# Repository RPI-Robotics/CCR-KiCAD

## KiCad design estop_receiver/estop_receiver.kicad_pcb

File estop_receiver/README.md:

# Emergency Stop Receiver

---

A custom board to wirelessly and securely interface with the Emergency Stop remote. Upon interfacing with the remote and confirming connection, the receiver will continuously scan for a heartbeat packet from the remote. If no heartbeat packet is received within 2 seconds, the receiver will trigger the failsafe to trigger the emergency stop. Upon receiving a STOP packet, the same emergency stop will trigger, pulling a high signal down to low within X ms.

This board is split into two different boards made to fabricate together and easily break apart from each other. One board is for LED indicators and the other is the board used to receive and interpret signals. Both are powered by 5V from the central power system.

**Status:** Version 1 Gerber and Drill files created. Ordering very soon (I hope).

## Schematic

---

**Rough breakdown:**

- Circuit takes two active low signals as input which are fed into an AND logic gate.

- AND gate controls an nMOS MOSFET which powers two Normally Open solid state relays.

- Upon the loss of one emergency stop signal, solid state relays shut off and indicator LED's switch.

## PCB Layout

---

PCB dimensions are 31mm x 56.5mm.

## ToDo List

---

- [x] Design PCB layout.

- [ ] Order board and parts.

- [ ] Assemble and test.

## Credits

---

Original design by James Qiu for RPI Robotics Club, 2026.

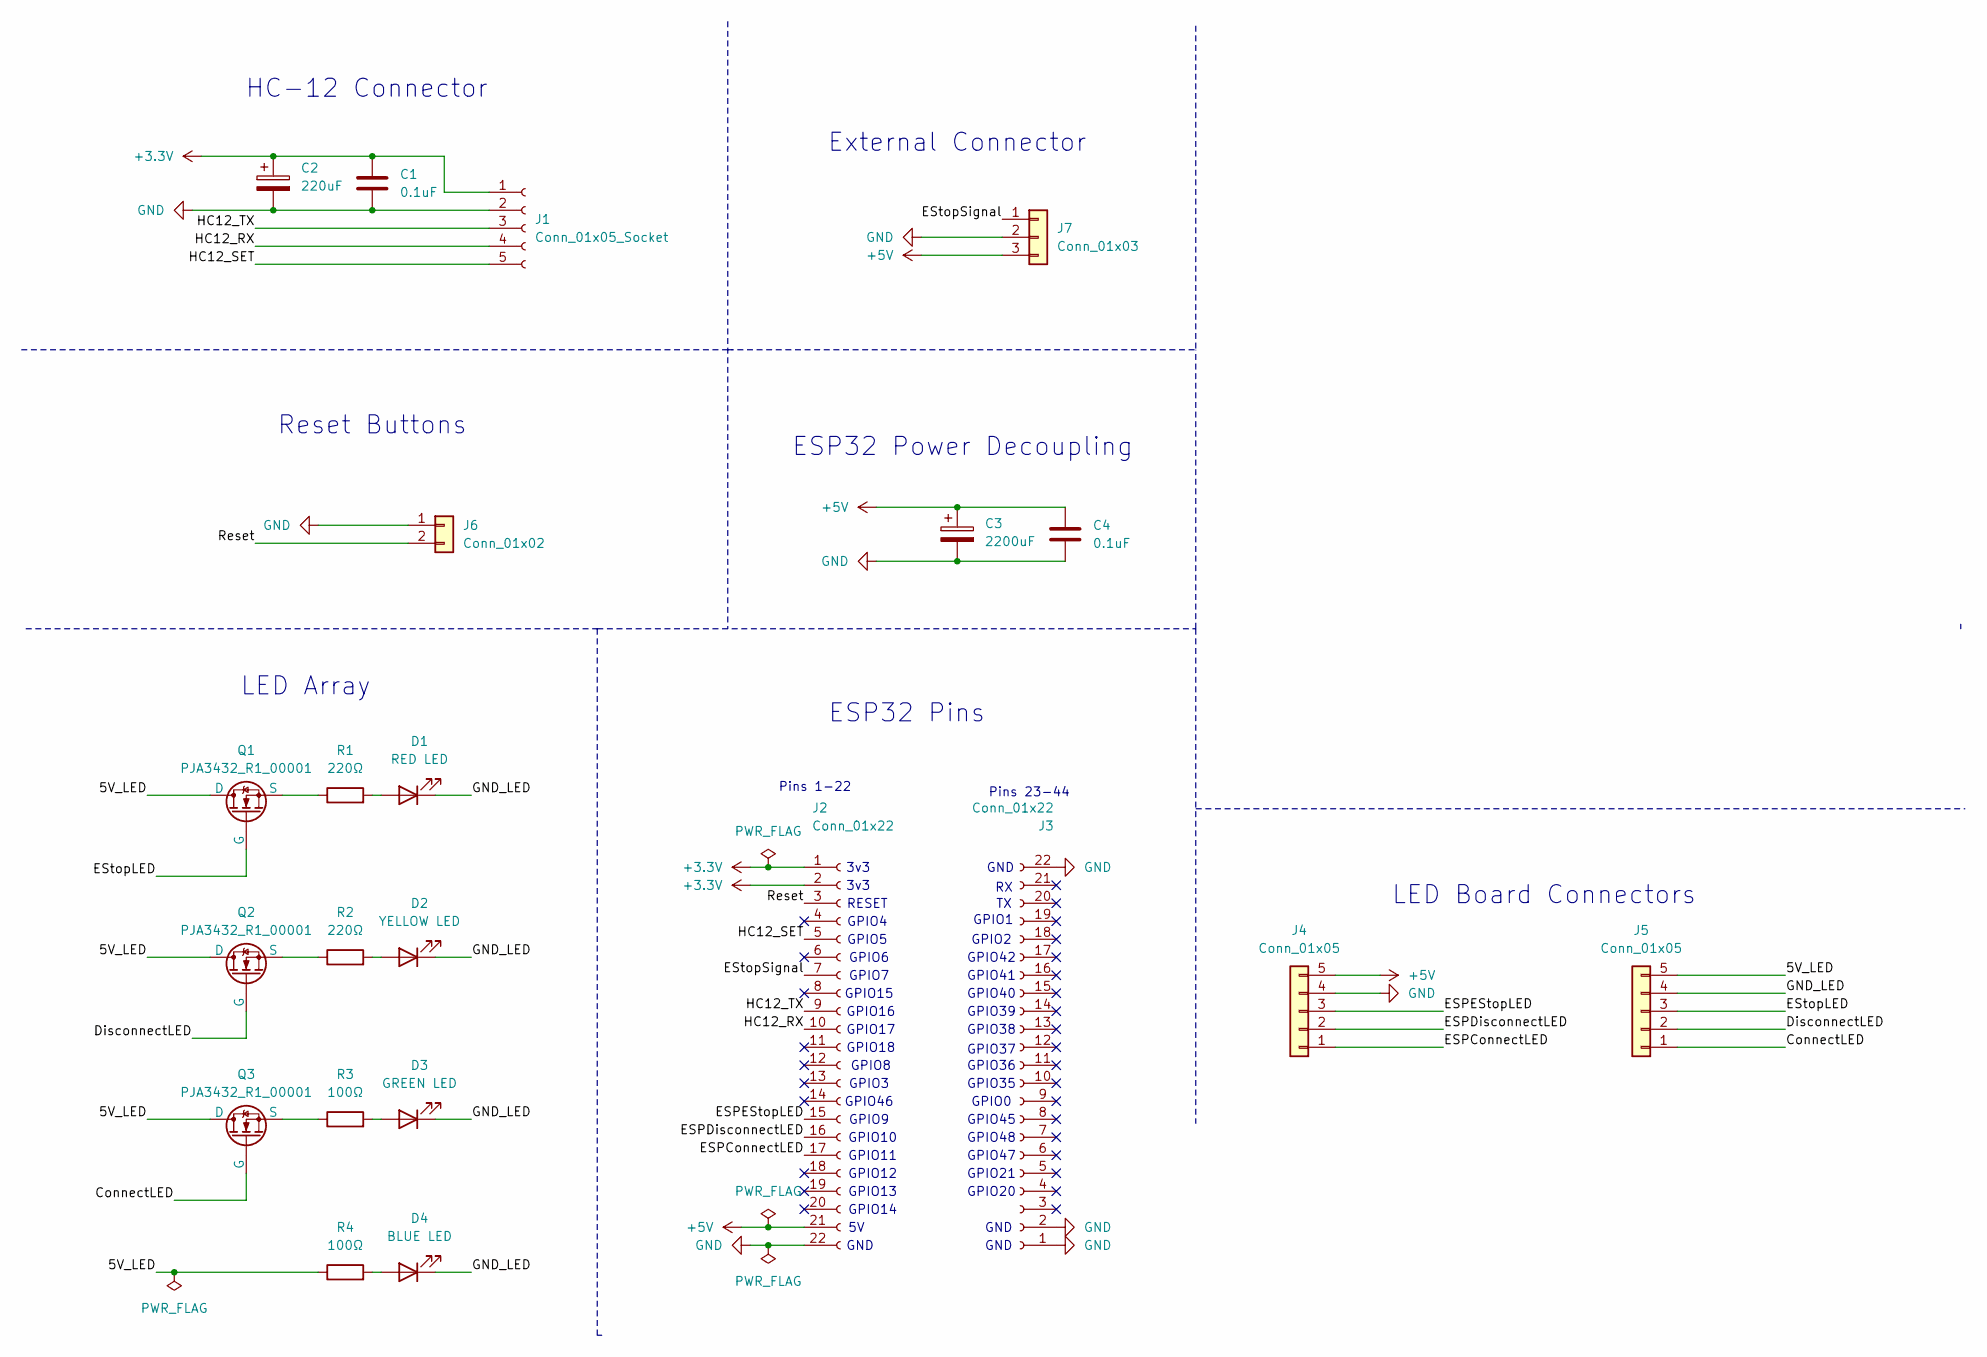
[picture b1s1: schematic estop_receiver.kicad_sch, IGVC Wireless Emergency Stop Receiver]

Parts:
C1, C4: 0.1uF; C_0805_2012Metric_Pad1.18x1.45mm_HandSolder
C2: 220uF; CP_Radial_D10.0mm_P2.50mm
C3: 2200uF; CP_Radial_D10.0mm_P2.50mm
D1: RED LED; LED_D3.0mm
D2: YELLOW LED; LED_D3.0mm
D3: GREEN LED; LED_D3.0mm
D4: BLUE LED; LED_D3.0mm
J1: Conn_01x05_Socket; PinSocket_1x05_P2.54mm_Vertical
J2, J3: Conn_01x22; PinSocket_1x22_P2.54mm_Vertical
J4, J5: Conn_01x05; JST_XH_B5B-XH-A_1x05_P2.50mm_Vertical
J6: Conn_01x02; JST_XH_B2B-XH-A_1x02_P2.50mm_Vertical
J7: Conn_01x03; JST_XH_S3B-XH-A_1x03_P2.50mm_Horizontal
Q1, Q2, Q3: PJA3432_R1_00001
R1, R2: 220Ω; R_0805_2012Metric_Pad1.20x1.40mm_HandSolder
R3, R4: 100Ω; R_0805_2012Metric_Pad1.20x1.40mm_HandSolder

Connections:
+3.3V: C1.1, C2.1, J1.1, J2.1, J2.2
+5V: C3.1, C4.1, J2.21, J4.5, J7.3
/5V_LED: J5.5, Q1.1 (D), Q2.1 (D), Q3.1 (D), R4.1
/ConnectLED: J5.1, Q3.2 (G)
/DisconnectLED: J5.2, Q2.2 (G)
/ESPConnectLED: J2.17, J4.1
/ESPDisconnectLED: J2.16, J4.2
/ESPEStopLED: J2.15, J4.3
/EStopLED: J5.3, Q1.2 (G)
/EStopSignal: J2.7, J7.1
/GND_LED: D1.1 (K), D2.1 (K), D3.1 (K), D4.1 (K), J5.4
/HC12_RX: J1.4, J2.10
/HC12_SET: J1.5, J2.5
/HC12_TX: J1.3, J2.9
/Reset: J2.3, J6.2
GND: C1.2, C2.2, C3.2, C4.2, J1.2, J2.22, J3.1, J3.2, J3.22, J4.4, J6.1, J7.2
unnamed: D1.2 (A), R1.2
unnamed: D2.2 (A), R2.2
unnamed: D3.2 (A), R3.2
unnamed: D4.2 (A), R4.2
unnamed: Q1.3 (S), R1.1
unnamed: Q2.3 (S), R2.1
unnamed: Q3.3 (S), R3.1

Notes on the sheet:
GPIO37
GPIO45
GPIO6
GPIO15
GPIO16
GPIO1
GPIO9
3v3
GPIO17
GPIO11
ESP32 Power Decoupling
GND
HC-12 Connector
GPIO12
GPIO4
GPIO46
GPIO0
GPIO3
ESP32 Pins
GPIO35
External Connector
GPIO41
Pins 23-44
Pins 1-22
GPIO36
GPIO7
GPIO38
GPIO8
GPIO18
GPIO47
RESET
LED Board Connectors
GPIO40
GPIO10
GPIO14
LED Array
GPIO42
GPIO5
GPIO21
GPIO39

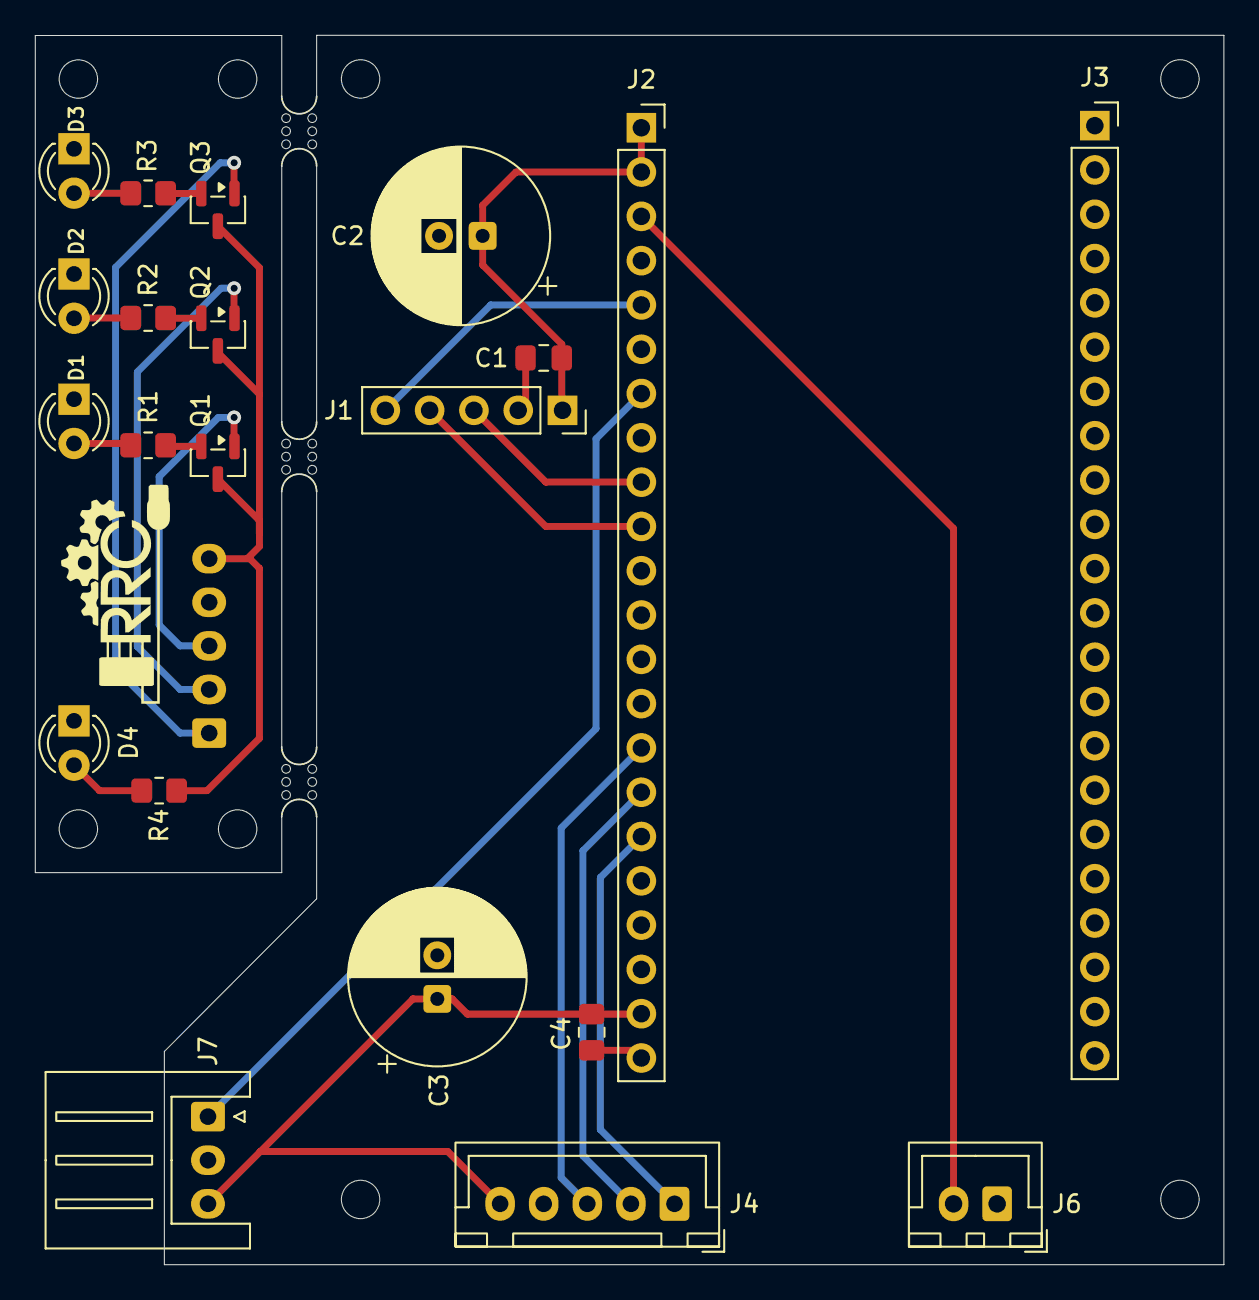
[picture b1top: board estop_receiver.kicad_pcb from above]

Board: 2 copper layers, 68.2 x 70.5 mm, 25 parts (1 on the bottom side), 23 nets.

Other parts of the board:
mouse-bite-2mm-slot, mouse-bite-2mm-slot#2, mouse-bite-2mm-slot#3: VAL**; mouse-bite-2mm-slot

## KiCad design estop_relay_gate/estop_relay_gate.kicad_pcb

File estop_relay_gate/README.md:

# Emergency Stop Relay Gate PCB

A custom board to take in two active low emergency stop signals and shut off relays instantaneously upon the loss of one emergency stop signals. I'm designing it in KiCAD to remove any risk of vehicle vibrations loosening solder connections.

The board mounts with 4 M2 screw holes on the corners. It is powered by 5V from the central power system, and takes in two inputs from the physical and wireless emergency stops. It outputs into two control lines for solid state relays powering 2 ODrive motor controllers.

**Status:** Version 1 Gerber and Drill files created. Ordering very soon (I hope).

## Schematic

**Rough breakdown:**

- Circuit takes two active low signals as input which are fed into an AND logic gate.

- AND gate controls an nMOS MOSFET which powers two Normally Open solid state relays.

- Upon the loss of one emergency stop signal, solid state relays shut off and indicator LED's switch.

## PCB Layout

PCB dimensions are 31mm x 56.5mm.

## ToDo List

- [x] Design PCB layout.

- [ ] Order board and parts.

- [ ] Assemble and test.

## Credits

Original design by James Qiu for RPI Robotics Club, 2026.

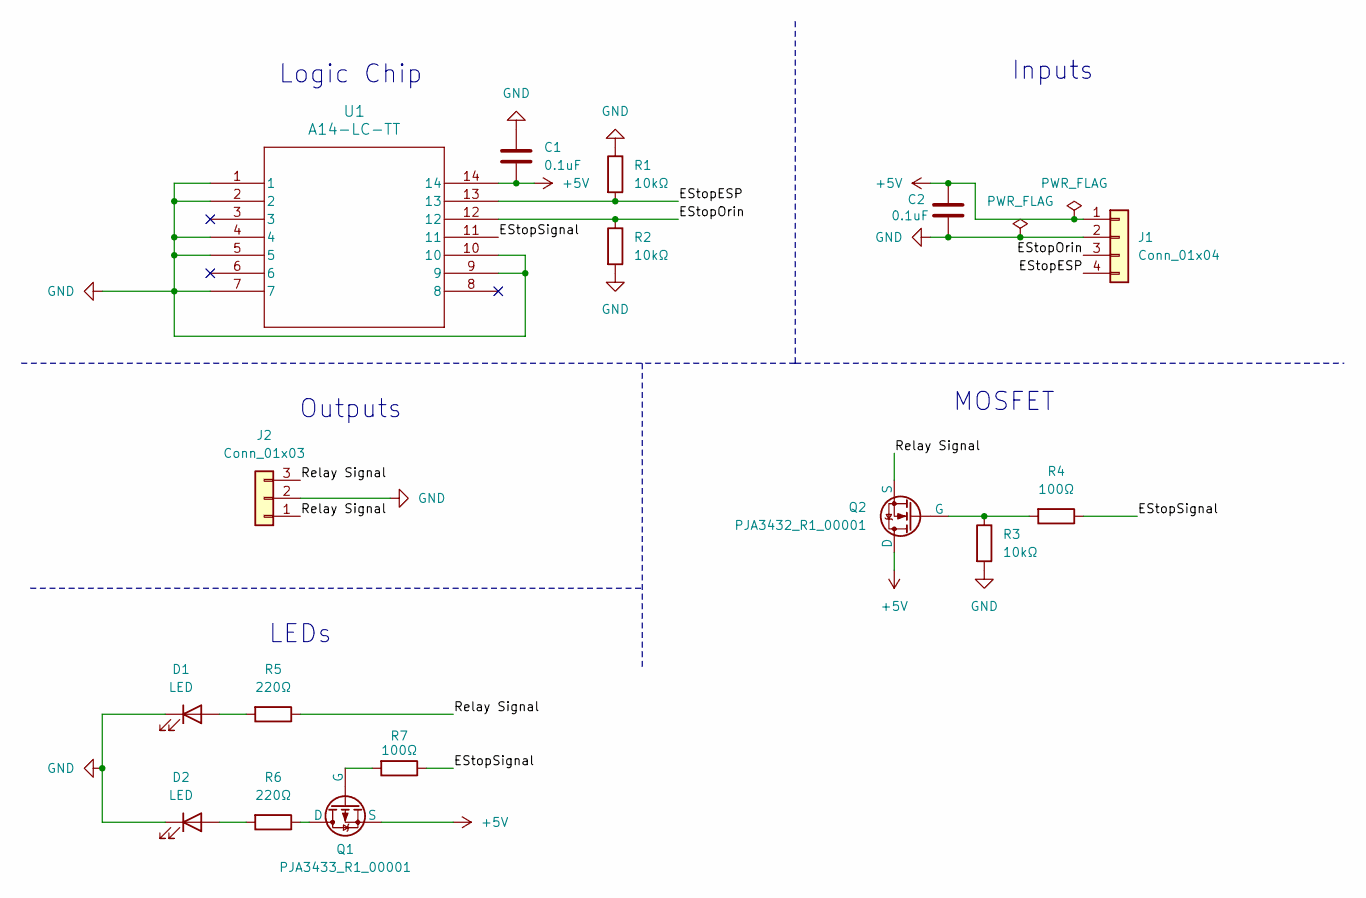
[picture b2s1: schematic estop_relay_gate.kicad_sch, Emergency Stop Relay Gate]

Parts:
C1, C2: 0.1uF; C_0805_2012Metric_Pad1.18x1.45mm_HandSolder
D1, D2: LED; LED_D3.0mm
J1: Conn_01x04; TerminalBlock_Phoenix_MKDS-1,5-4_1x04_P5.00mm_Horizontal
J2: Conn_01x03; TerminalBlock_Phoenix_MKDS-1,5-3_1x03_P5.00mm_Horizontal
Q1: PJA3433_R1_00001
Q2: PJA3432_R1_00001
R1, R2, R3: 10kΩ; R_0805_2012Metric_Pad1.20x1.40mm_HandSolder
R4, R7: 100Ω; R_0805_2012Metric_Pad1.20x1.40mm_HandSolder
R5, R6: 220Ω; R_0805_2012Metric_Pad1.20x1.40mm_HandSolder
U1: A14-LC-TT; A14-LC-TT_ASM

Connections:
+5V: C1.2, C2.1, J1.1, Q1.3 (S), Q2.1 (D), U1.14; also elsewhere on the board
/EStopESP: J1.4, R1.2, U1.13
/EStopOrin: J1.3, R2.1, U1.12
/EStopSignal: R4.1, R7.1, U1.11; also elsewhere on the board
/Relay Signal: J2.1, J2.3, Q2.3 (S), R5.1
GND: C1.1, C2.2, D1.1 (K), D2.1 (K), J1.2, J2.2, R1.1, R2.2, R3.2, U1.1, U1.2, U1.4, U1.5, U1.7, U1.9, U1.10
unnamed: D1.2 (A), R5.2
unnamed: D2.2 (A), R6.2
unnamed 8: Q1.1 (D), R6.1; also elsewhere on the board
unnamed: Q1.2 (G), R7.2
unnamed: Q2.2 (G), R3.1, R4.2

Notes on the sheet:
Logic Chip
MOSFET
Inputs
Outputs
LEDs

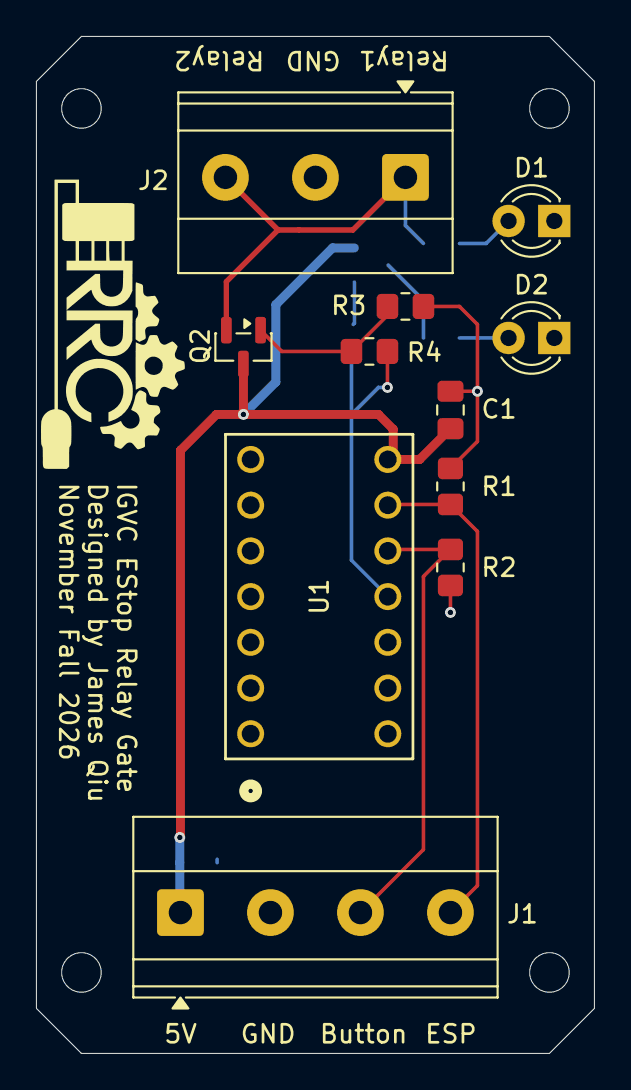
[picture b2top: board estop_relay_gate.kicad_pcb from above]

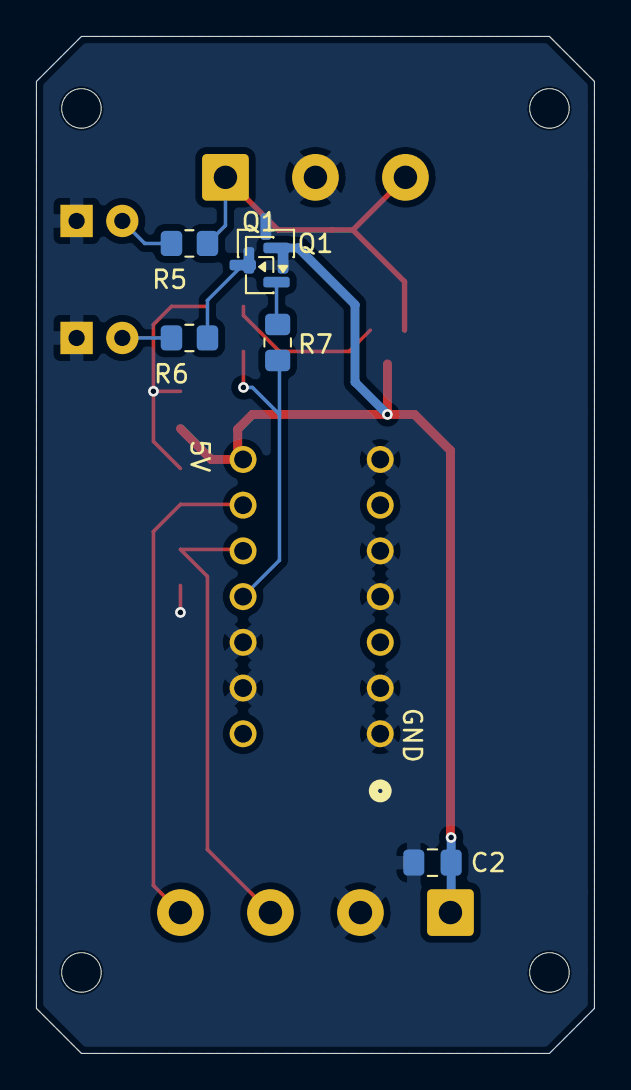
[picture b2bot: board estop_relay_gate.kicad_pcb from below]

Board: 2 copper layers, 31.0 x 56.5 mm, 17 parts (6 on the bottom side), 11 nets.

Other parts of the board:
Q1#2: AO3401A; SOT-23

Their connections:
+5V: Q1#2.2 (S); also elsewhere on the board
/EStopSignal: Q1#2.1 (G); also elsewhere on the board
unnamed 8: Q1#2.3 (D); also elsewhere on the board

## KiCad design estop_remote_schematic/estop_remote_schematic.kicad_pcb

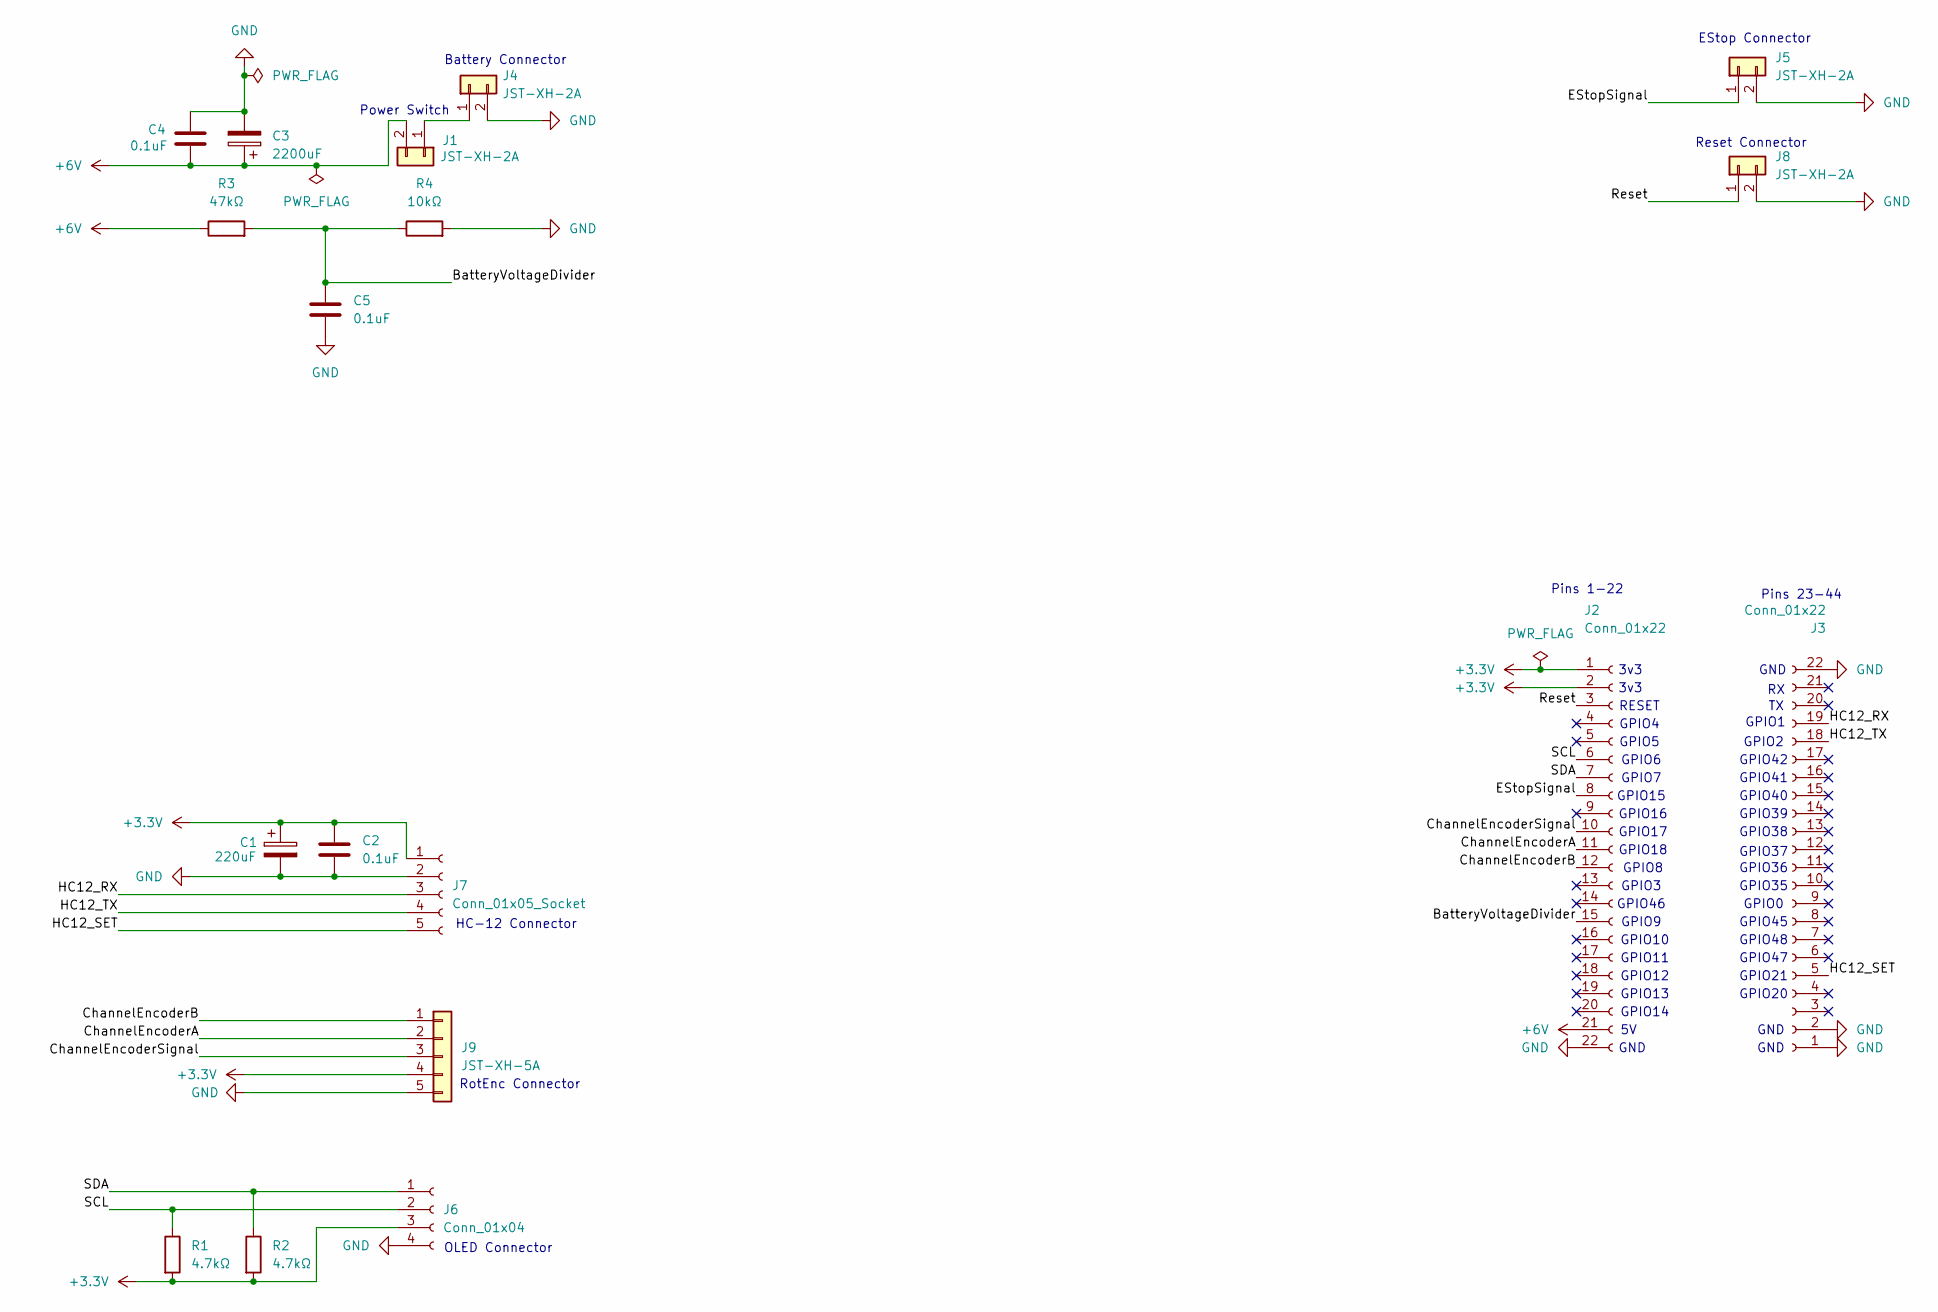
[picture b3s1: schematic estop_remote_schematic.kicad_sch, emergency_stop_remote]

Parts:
C1: 220uF; CP_Radial_D7.5mm_P2.50mm
C2, C4, C5: 0.1uF; C_0603_1608Metric_Pad1.08x0.95mm_HandSolder
C3: 2200uF; CP_Radial_D10.0mm_P5.00mm
J1, J4, J5, J8: JST-XH-2A; JST_XH_B2B-XH-A_1x02_P2.50mm_Vertical
J2, J3: Conn_01x22; PinSocket_1x22_P2.54mm_Vertical
J6: Conn_01x04; JST_XH_B4B-XH-A_1x04_P2.50mm_Vertical
J7: Conn_01x05_Socket
J9: JST-XH-5A; JST_XH_B5B-XH-A_1x05_P2.50mm_Vertical
R1, R2: 4.7kΩ; R_0805_2012Metric_Pad1.20x1.40mm_HandSolder
R3: 47kΩ; R_0805_2012Metric_Pad1.20x1.40mm_HandSolder
R4: 10kΩ; R_0805_2012Metric_Pad1.20x1.40mm_HandSolder

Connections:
+3.3V: C1.1, C2.1, J2.1, J2.2, J6.3, J7.1, J9.4, R1.2, R2.2
+6V: C3.1, C4.2, J1.2, J2.21, R3.1
/BatteryVoltageDivider: C5.1, J2.15, R3.2, R4.1
/ChannelEncoderA: J2.11, J9.2
/ChannelEncoderB: J2.12, J9.1
/ChannelEncoderSignal: J2.10, J9.3
/EStopSignal: J2.8, J5.1
/HC12_RX: J3.19, J7.3
/HC12_SET: J3.5, J7.5
/HC12_TX: J3.18, J7.4
/Reset: J2.3, J8.1
/SCL: J2.6, J6.2, R1.1
/SDA: J2.7, J6.1, R2.1
GND: C1.2, C2.2, C3.2, C4.1, C5.2, J2.22, J3.1, J3.2, J3.22, J4.2, J5.2, J6.4, J7.2, J8.2, J9.5, R4.2
unnamed: J1.1, J4.1

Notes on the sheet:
GPIO1
GPIO10
GPIO14
GPIO45
Battery Connector
GPIO35
GND
Pins 23-44
Reset Connector
GPIO38
GPIO21
GPIO39
GPIO5
GPIO47
GPIO36
GPIO48
GPIO7
GPIO4
HC-12 Connector
GPIO46
GPIO40
GPIO6
GPIO16
GPIO15
RESET
GPIO41
GPIO9
GPIO12
RotEnc Connector
GPIO11
3v3
GPIO8
GPIO0
GPIO18
GPIO17
Pins 1-22
GPIO13
GPIO2
OLED Connector
GPIO42

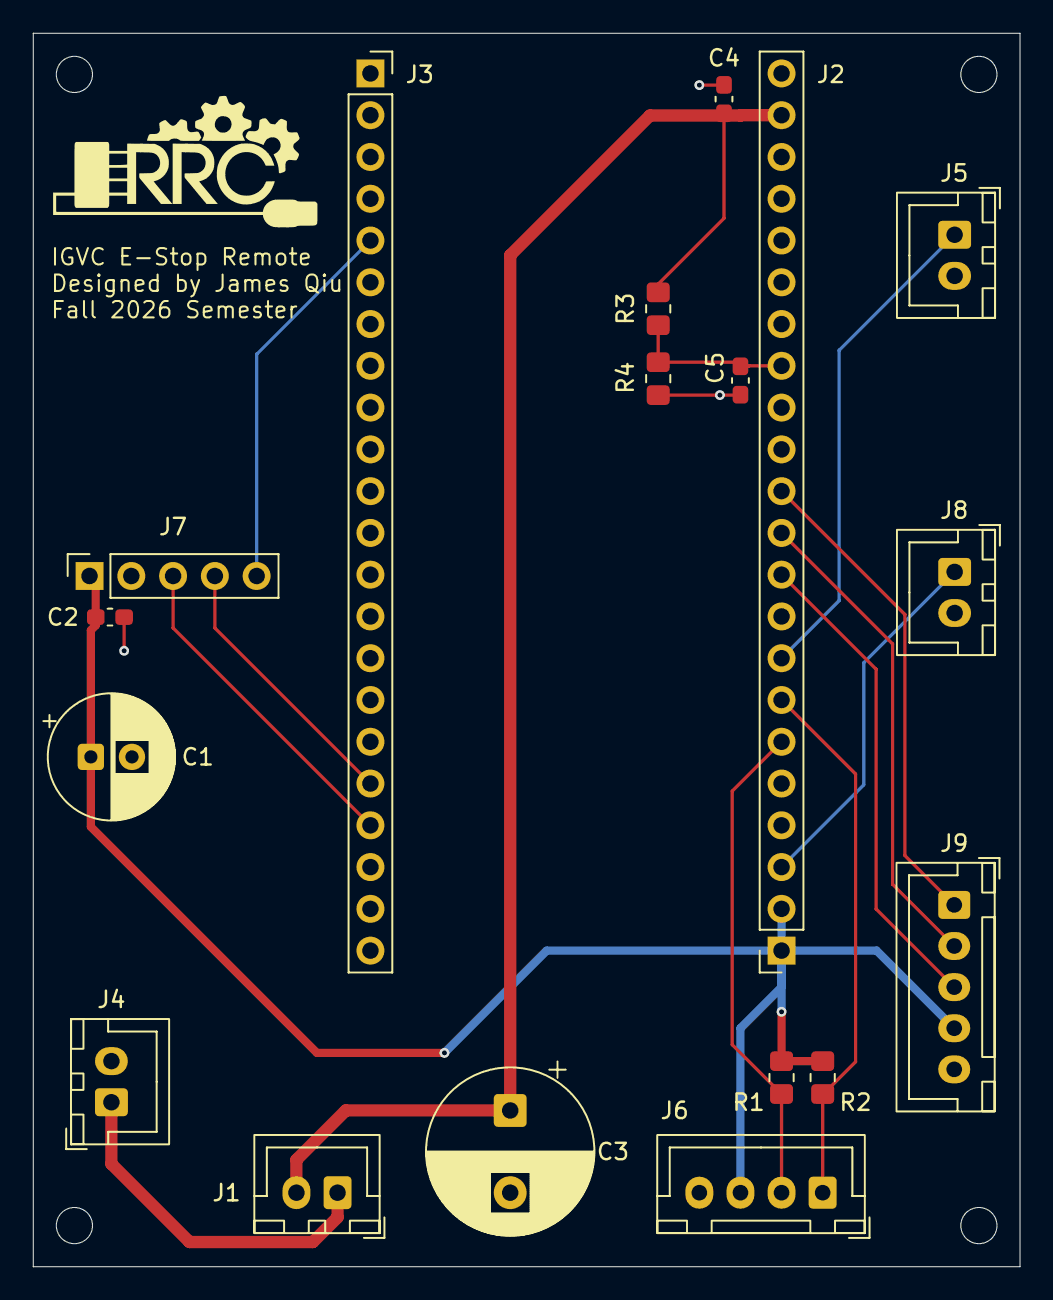
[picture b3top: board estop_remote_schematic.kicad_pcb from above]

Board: 2 copper layers, 60.0 x 75.0 mm, 18 parts (0 on the bottom side), 15 nets.
